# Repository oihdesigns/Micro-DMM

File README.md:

# Update Late August '25: 
I've recently started a new job. It's great, but has longer hours than my previous job. This will negatively affect the amount of time I put into this project...

# Micro-DMM

This is the PCB design and code for a 4.5 digit DMM/ instrumentation module. It is designed and written primairly for Arduino-style development boards.

I've developed this DMM in my work testing and troubleshooting electronics to make my life easier. 

I've had Deep-Wiki index my documentation. It did a mostly okay job. You can read its summary here:

## The main features are:

- The most recent designs have **open-lead detection in voltmeter mode**. I believe this makes it the first voltmeter in exisitance that can automatically, safely, and positively tell the difference between "there is low impedance between these points" vs "current does not and can not flow between these two points." Please see the white paper for details. 
- Using keyboard emulation to directly type values into a computer for me. (Extremely useful when troubleshooting a populated PCB - you can quickly ohm out both the problem board and a good one directly into Excel to look for different impedances between given contacts.)
- Very sensitive low-resistance readings (accurate to better than 0.01 Ohms with proper lead zeroing).
- LED blinks when I'm reading logic level voltage or higher.
- Simultaneous current and voltage measurement abilities (requires a Hall sensor-based ammeter module). 
- Data logging for current and voltage, with customizable triggers to autolog both.

## Raspberry Pi user interface

The repository now includes a Raspberry Pi-friendly interface that mirrors the firmware display and logging features. The UI is written in Python using Tkinter so it ships with Raspberry Pi OS and can run directly on the framebuffer or under X11. To start the dashboard with the built-in demo generator run:

```
python3 -m raspi_port.app
```

In deployment the measurement host should feed real readings to the `MicroDmmApp` class instead of the demo thread. The window presents the same information rendered by `updateDisplay()`—live voltage or resistance with min/max tracking, current when enabled, the active mode, timestamps, delta/null information, and log counters. Interaction hotkeys replace the touch panel:

| Function | Touch color | Hotkey | Description |
| --- | --- | --- | --- |
| Mode cycle | Red | `M` | Advances through the measurement modes. |
| Manual log | Green | `L` | Appends the most recent sample buffer to `~/micro_dmm_logs/data.csv`. |
| Auto log export | – | `A` | Writes the auto-log buffer to `~/micro_dmm_logs/data_autologged.csv`. |
| Min/Max reset | Blue | `Z` | Clears the stored extrema, just like tapping “Min/Max”. |
| Type/Δ | Yellow | `T` | In *Type* mode it writes the displayed value to `typed_entries.txt`; otherwise it arms the delta/null workflow. |

On a Raspberry Pi you can optionally map these controls to hardware buttons by defining a `MICRO_DMM_GPIO` environment variable before launching the program. The value is a comma-separated list such as `mode=5,manual_log=6,auto_log=13,minmax=19,type=26`. Each entry binds a GPIO pin (using `gpiozero.Button`) to the corresponding action.

All log exports stay on the Pi’s filesystem under `~/micro_dmm_logs/`. The CSV layouts match the firmware’s `logCurrentData()` and `autologArraysToCSV()` routines so downstream tooling continues to work. The `typed_entries.txt` file replaces the USB keyboard emulator and captures the same formatted text that would have been “typed” into a host PC, while also echoing it to stdout for quick clipboard-style use.

I have a long and detailed write-up of the circuitry design on my personal website: https://www.oihdesigns.com/arduino-multimeter-project

There are a couple videos here:
https://youtu.be/rzj-ar2Qv_A
and here:
https://youtu.be/hZ4eH-7RNsU

Here are more photos:

## Design Prioities and Compromises:
This meter is designed to complement and support the more expensive equimpent generally found in a lab, rather than replace it. With that in mide, I've made the following design decisions on my priorites:

### Minimal Protections
- The voltmeter circuitry is not designed to measure amplitudes higher than is dangerous to humans. By not designing a tool that is supposed to keep people safe I can dramatically simplify and shrink the design. (The said, I've nailed the voltmeter circuit with a 1000V megaohmmeter. No problem.)
- Likewise, the resistance circuit can be damaged if you accidentally measure too much /unregulated voltage. This is a tradeoff for a very fast and accurate autoranging ohmmeter circuit that can accurately read from less than 0.01 to more than 5,000,000 Ohms. 

### Streamlined Functions
- There is no built in ammeter, inductance, or capacitance function. Ammeter function is easily added as needed with either an off-the-shelf module, or a low value resistor across the voltmeter. There isn't an easy way to add indutance or capacitance. I don't use any of these often enough for them to be worth taking up the PCB space.  

## Current Support:
As of writing I have functional versions (I confirmed the core functions work) that support the:
- Arduino Uno R4
- Arduino Giga (with or without the display shield)
- Arduino ESP32 Nano (via jumpers)
- Seeed Studio XIAO RA4M1 (same processer as the Uno R4)
- I have partial function on a direct computer (Windows 11) interface with a FT232H breakout board (AdaFruit makes a nice one). I can see the data lines and it looks like most of the logic works, more or less. It's a proof of concept port and a test for "can I tell the AI to take an Arduino sketch and port it to Python" (the answer is far more yes than it use to be).
  -  That said, it's very slow (reading in at 2-3sps). I'm not sure how to optimize this, and speeding it up is not an immediate priority. 

# Future Plans:

## Major Function Things to Address:
- Writing to MicroSD cards over the AUX SPI Bux on the RA4M1 XIAO boards. I set this up and tested it, but it didn't work and needs to be troubleshot.
- Getting the code to run on the XIAO RP2350 board. It compiles but does not run. 

## Potential Refinements To-Do List:
- Revise the PCB design to shrink the physical size (the current design was made with hand-soldering in mind). This would involve:
  - Smaller footprint components for things like the pullup resistors.
  - Dedicated multiple transistor packages for the switching functions rather than the discreet components.
  - There are probably other ways to shrink the design.
  - There is some potential performance improvement room to the analog circuit if I take advantage of the ADS1115's max input voltage of ~6.144vdc instead of 5vdc.
- There is always room for cleanup in the code to make it more elegant. 

## Ideas for Expanding on the Current Function / :
- Make a version that uses an ADS1256 instead of the ADS1115 to support measurements speeds up to 30,000 samples/second and resolutions of up to 24bits. (I have had proof-of-concept success with this using a Raspberry PI ADS1256 hat.)
- Make a version that runs off a Raspberry Pi.
- Implement WiFi/Bluetooth features on the boards that support it.
- Implement DAC output as a simple function generator for the boards that support it.
- Add a jumper on the PCB and write the code to allow four-wire resistance readings.

If you're interested in helping develop this please feel free to reach out. 

# FAQ:
- Q: What is the logic voltage?
  - A:  The current PCB works for either 3.3 or 5vdc. 

- Q: Is there voltage isolation on the USB?
  - A: There is enough isolation (500K Ohms) that you will not hurt anything by measuring voltage (in either polarity) on something connected to the wall while the meter is also connected to the wall, but not enough to prevent ground loops from interfering with measurements. See the longer, full write up on my website, and then buy the Adafruit USB voltage isolation board.

- Q: The Adafruit isolation board says "100mA." What does the meter draw?
  - A: With the XIAO RA4M1, 50-60mA typical when measuring voltage. Closer to 100mA when measuring resistance. The resistance circuit goes into low-power mode several seconds after being open (except in a no-sleep mode).

- Q: Does it work on an Arduino Uno R3?
  - A: As a basic meter, yes, but there's no keyboard emulation.    

- Q: Can I buy one?
  - A: Eventually, yes, probably? I do not have a current timeline for bringing these to market. If you want one please reach out to me. If you want to hand-solder it yourself I can sell you a single PCB and maybe some of the components with higher individual costs.

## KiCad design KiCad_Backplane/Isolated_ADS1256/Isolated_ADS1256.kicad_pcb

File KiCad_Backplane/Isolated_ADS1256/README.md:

# Isolated ADS1256 — rev A

This is an isolated 24-bit ADC board, 95 × 62 mm with 4 layers. The ADS1256, its reference, clock and LDOs all sit on the isolated side. SPI crosses a TI ISO7762 (5 kVrms reinforced, 4 forward / 2 reverse channels). Power crosses a Murata MEJ1S0509SC (5 V in, 9 V out, 5.2 kVDC rated, 3 pF isolation capacitance).

Status: generated, routed and checked: ERC 0, DRC 0 at all severities, 0 unconnected, schematic parity 0. It has not been ordered or tested on hardware.

## Channels

| ADS1256 inputs | Function | Scaling | Suggested setup |
|---|---|---|---|
| AIN0 / AIN1 | ±250 VDC differential | Each leg is 3 × 825k + 10k, returned to COM. k = 10k / 2.485 MΩ = 1/248.5, so 250 V gives 1.006 V. **Vin = Vdiff × 248.5** | BUFEN = 1, PGA 4: ±1.25 V full scale = ±310 V |
| AIN2 / AIN3 | 0.1 Ω shunt (RS1, TLMQ2HDR10FTE, 1.5 W) | Kelvin taps through 100 Ω, with 10 nF C0G across the pair. **I = Vdiff / 0.1** | PGA 8: ±625 mV full scale = ±6.25 A. The shunt is rated about 3.8 A continuous. |
| AIN4–7, AINCOM | Broken out on J4 | Each through 1k | — |
| D0–D3 | ADS1256 GPIOs, on J5 (3.3 V logic, isolated) | — | — |

## COM: the isolated reference (read this before connecting anything)

- **COM sits 1.5 V above GNDI.** GNDI is the ADC's own ground. U5 (OPA333) buffers COM, with 47 Ω and 10 µF on its output. This puts every input in the middle of the ADS1256 buffered input range (GNDI to AVDD−2 V, i.e. 0–3 V), so both the shunt and the divider can swing negative relative to COM.
- **COM is the node the measured circuit connects to.** JP1 is bridged by default and ties the shunt's I− end to COM. The shunt therefore defines where the isolated side sits.
- **Do not connect GNDI to the measured circuit as well.** That would short the COM buffer.
- **Common-mode limit:** each HV terminal must stay within about ±370 V of COM. The shunt must stay within about ±1.2 V of COM, which it does when JP1 is bridged.

## Connectors

- **J1 (host):** 5V, GND, VIO, ~SYNC, ~CS, DIN (MOSI), SCLK, ~DRDY, DOUT (MISO), GND.
  - VIO is your logic rail, 2.25–5.5 V.
  - 5 V input current is roughly 80 mA.
  - The isolator outputs default high, so ~CS and ~SYNC idle high when the host is off.
- **J4 (isolated analog):** A4, A5, A6, A7, AINCOM (each through 1k), COM, GNDI, 5VA (AVDD; keep the load at or below 5 mA).
- **J5 (isolated GPIO):** D0, D1, D2, D3, 3V3 (DVDD), GND.
- **J2:** HV+ / HV− screw terminal.
- **J3:** I+ / I− screw terminal.

## Firmware notes

- **~RESET** is held high by a 10k pull-up. Use the RESET command (0xFE) after power-up.
- **D0/CLKOUT** outputs 7.68 MHz after reset. Clear CLK1:0 in ADCON unless you want the clock on J5.
- **Input buffer:** use BUFEN = 1. The divider has about 10 kΩ source impedance, which is too high for the unbuffered input (about 150 kΩ / PGA).

## Isolation

- **Barrier width:** a 5.6 mm copper-free band, set by the MEJ1 module's 5.9 mm pin gap. The ISO7762 has 8 mm internally.
- **HV divider area:** no copper on In1, In2 or B.Cu underneath it. The HV netclass enforces 1.5 mm clearance on F.Cu.
- **Rating:** none of this is a certified insulation rating. Treat the board as basic insulation for a few hundred volts working, and use nylon hardware in the isolated-side mounting holes.

## Files and regenerating

- `tools/design.py` is the single source of truth.
- `tools/make_lib.py` generates `Isolated_ADS1256.kicad_sym` (ADS1256, MEJ1S0509SC, TPS7A4901).
- `tools/gen_sch.py` writes the schematic. `tools/gen_pcb.py` writes the placed, unrouted board. **Running gen_pcb wipes the routing.**
- **Routing flow** (needs a `kicad-cli api-server` running; see `tools/kipc.py`), run in this order:
  1. `stitch_planes.py`
  2. `retry.py --via` for the two LDO thermal pads
  3. `route_pass.py`
  4. `manual_ain.py`: hand-drawn AIN4–7 lanes and Kelvin taps, then +5VA and COM re-routed
  5. `post_silk.py`
  6. a manual U5 GND-to-R6 tie
- Snapshots of each stage are in `build/`.
- Output files: `Isolated_ADS1256_schematic.pdf` and `Isolated_ADS1256_BOM.csv`.

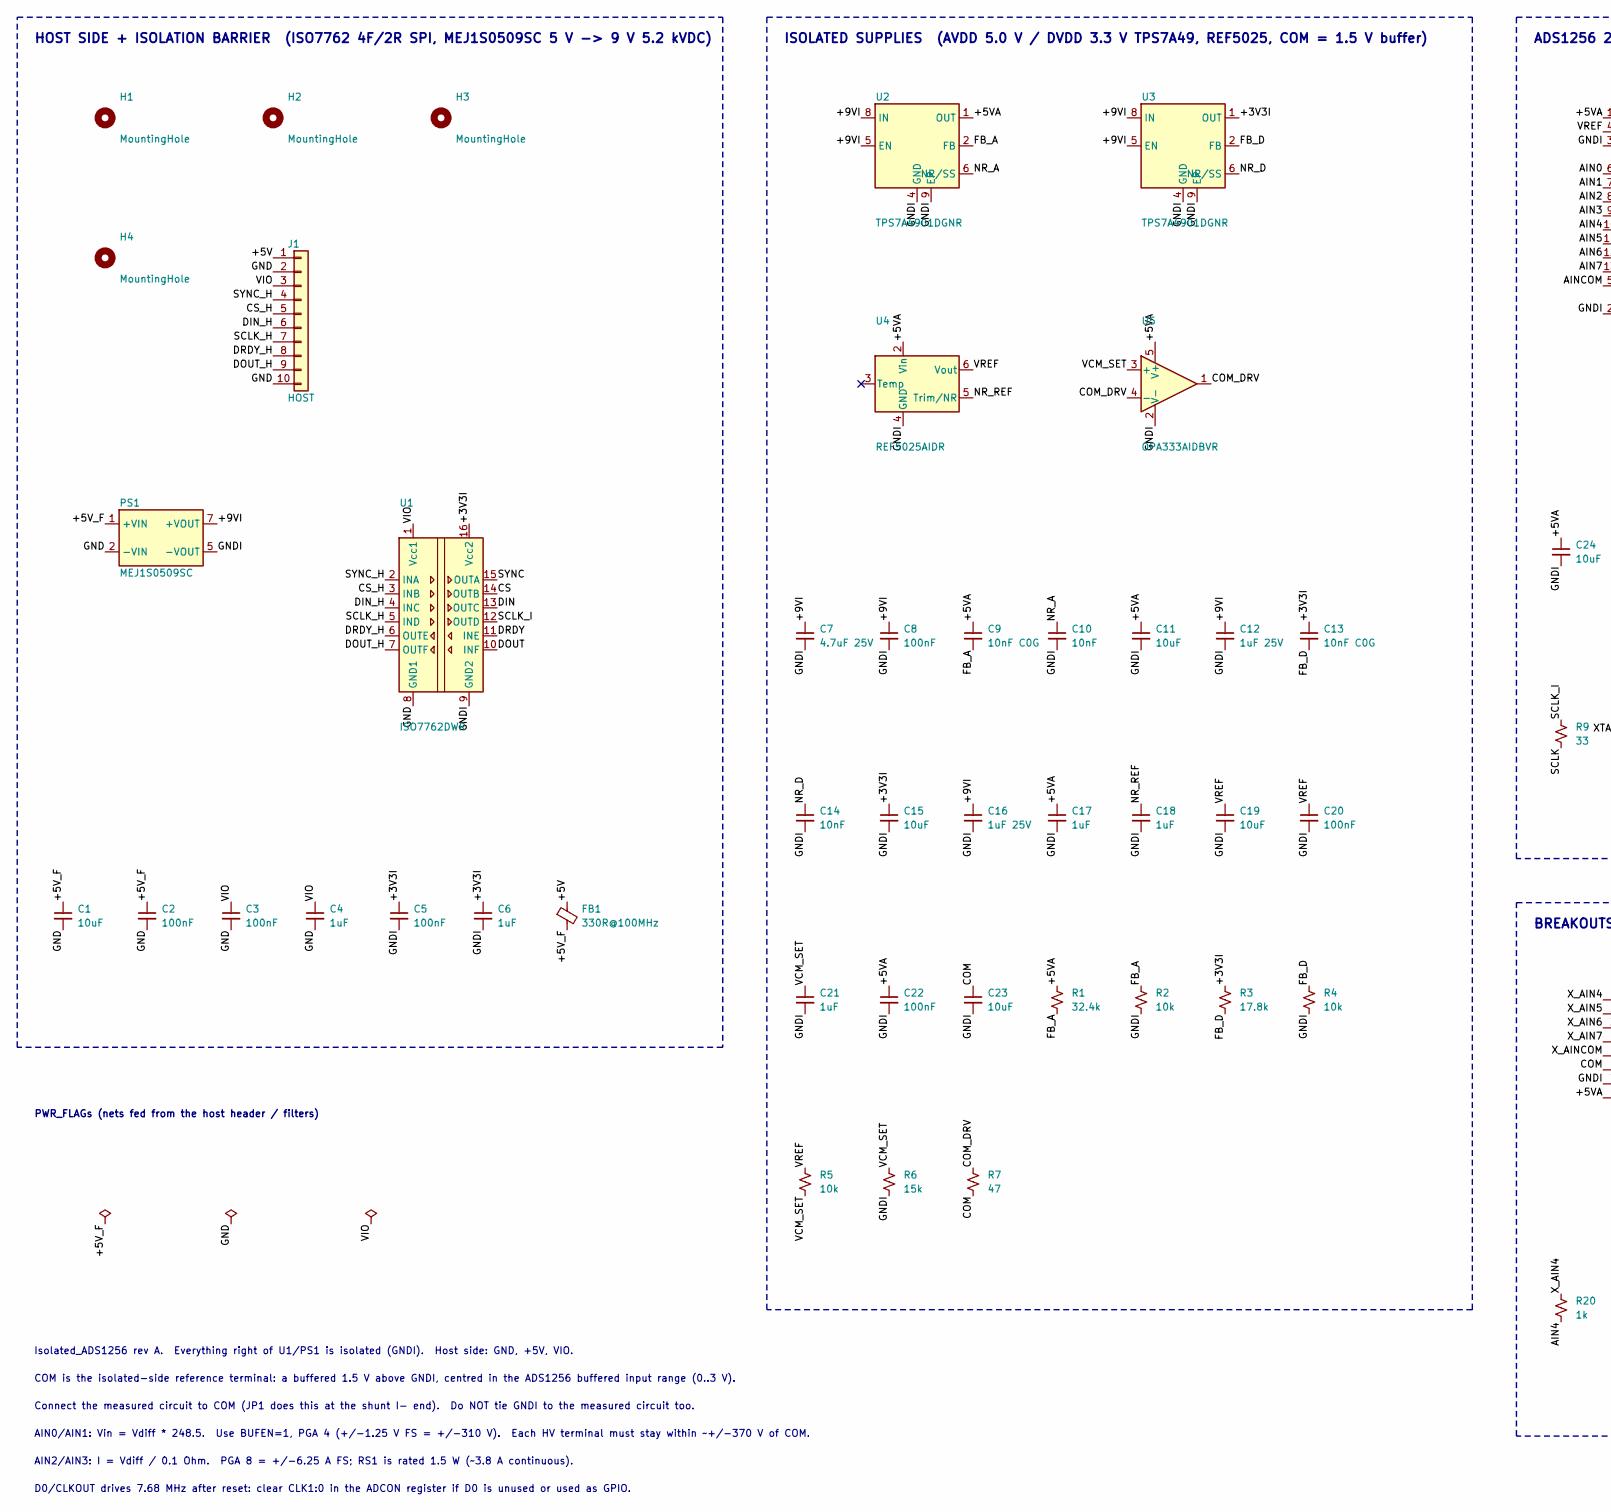
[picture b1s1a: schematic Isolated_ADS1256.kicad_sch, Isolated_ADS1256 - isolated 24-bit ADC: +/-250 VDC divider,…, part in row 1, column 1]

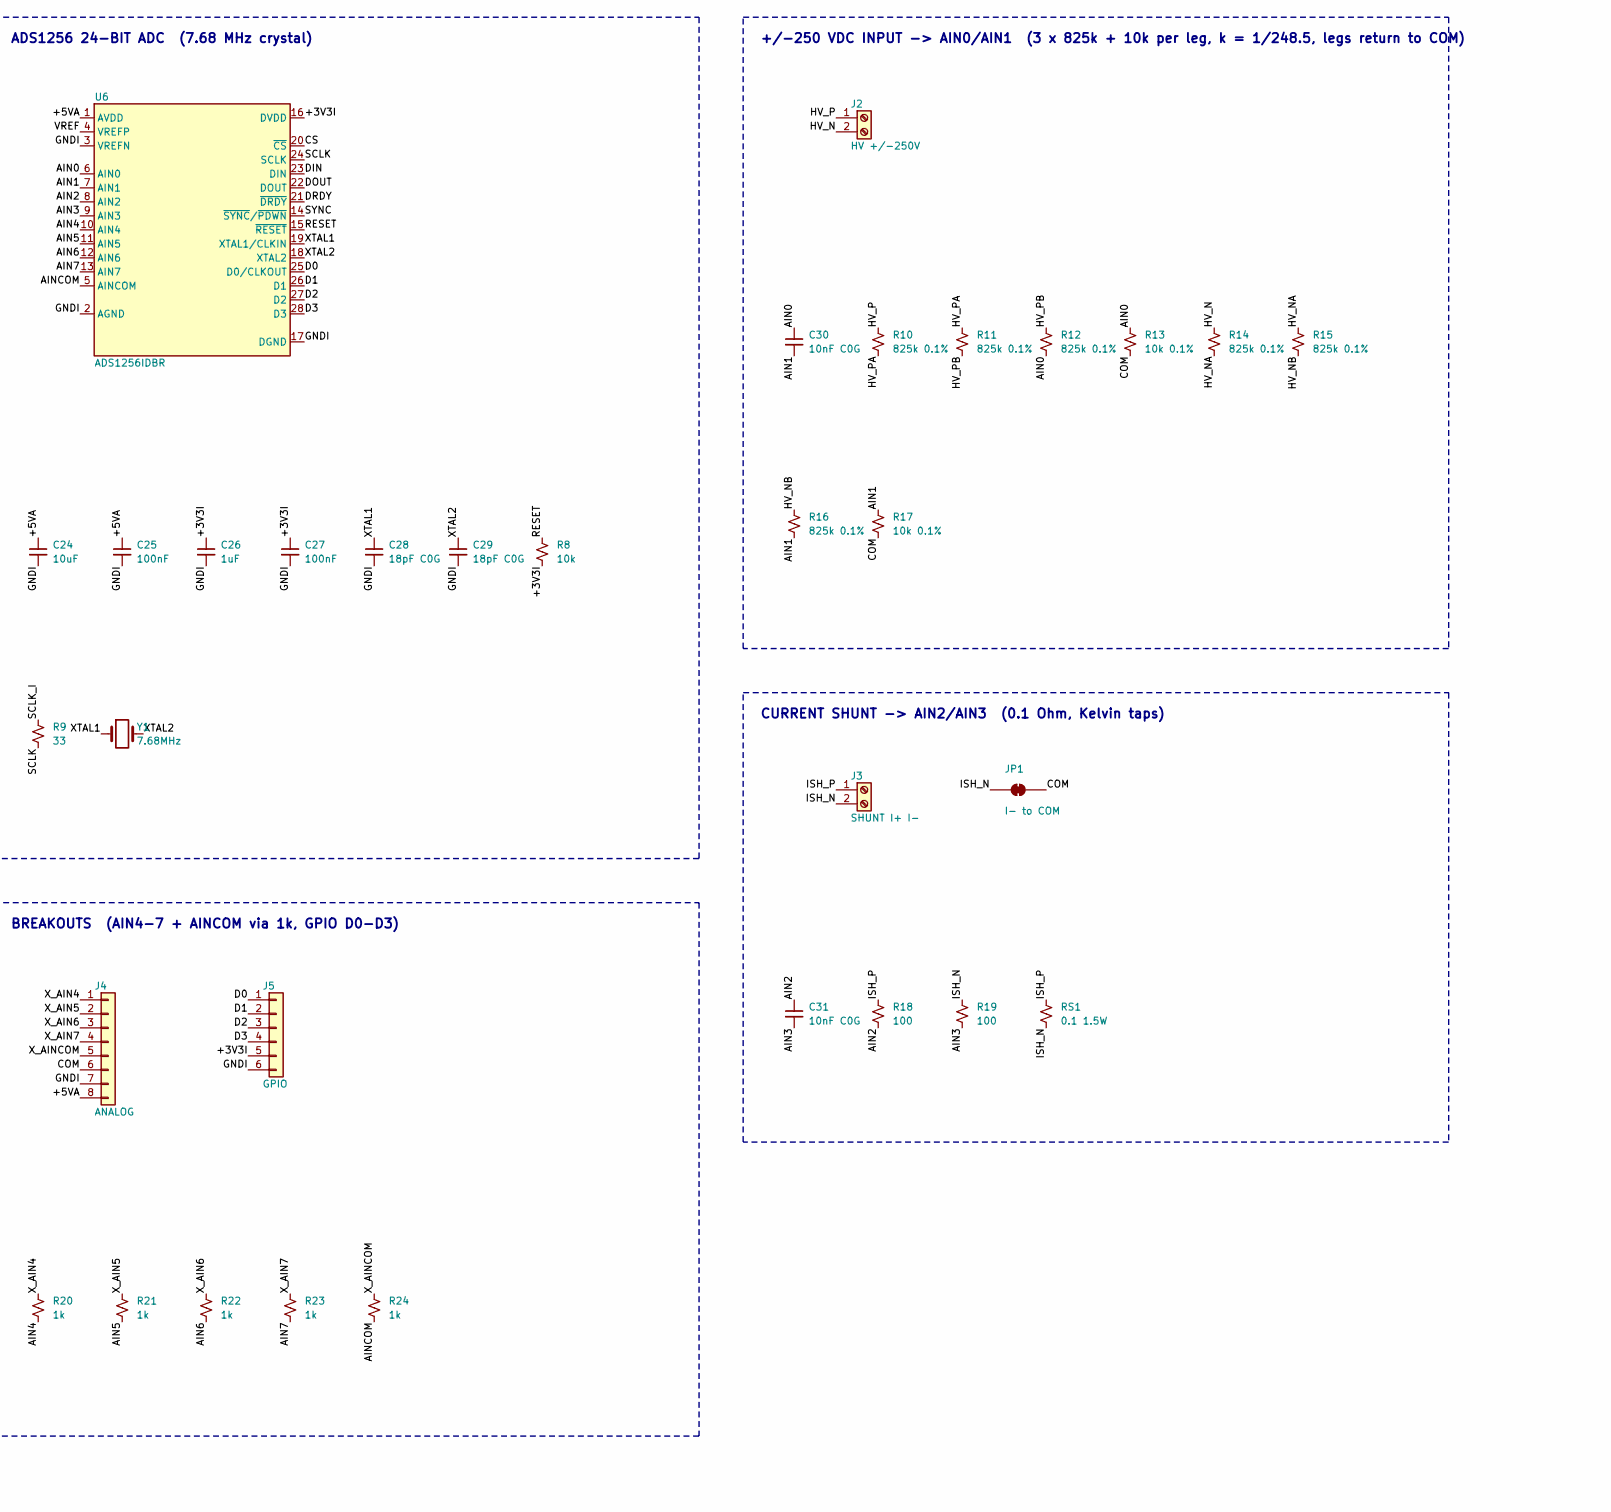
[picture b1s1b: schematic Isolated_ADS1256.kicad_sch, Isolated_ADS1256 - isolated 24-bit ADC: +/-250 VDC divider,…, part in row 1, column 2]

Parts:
C1, C11, C15, C19, C23, C24: 10uF; C_0805_2012Metric_Pad1.18x1.45mm_HandSolder
C2, C3, C5, C8, C20, C22, C25, C27: 100nF; C_0603_1608Metric_Pad1.08x0.95mm_HandSolder
C4, C6, C17, C18, C21, C26: 1uF; C_0603_1608Metric_Pad1.08x0.95mm_HandSolder
C7: 4.7uF 25V; C_0805_2012Metric_Pad1.18x1.45mm_HandSolder
C9, C13: 10nF C0G; C_0603_1608Metric_Pad1.08x0.95mm_HandSolder
C10, C14: 10nF; C_0603_1608Metric_Pad1.08x0.95mm_HandSolder
C12, C16: 1uF 25V; C_0603_1608Metric_Pad1.08x0.95mm_HandSolder
C28, C29: 18pF C0G; C_0603_1608Metric_Pad1.08x0.95mm_HandSolder
C30, C31: 10nF C0G; C_0805_2012Metric_Pad1.18x1.45mm_HandSolder
FB1: 330R@100MHz; L_0805_2012Metric_Pad1.05x1.20mm_HandSolder
H1, H2, H3, H4: MountingHole; MountingHole_3.2mm_M3
J1: HOST; PinHeader_1x10_P2.54mm_Vertical
J2: HV +/-250V; TerminalBlock_RND_205-00232_1x02_P5.08mm_Horizontal
J3: SHUNT I+ I-; TerminalBlock_RND_205-00232_1x02_P5.08mm_Horizontal
J4: ANALOG; PinHeader_1x08_P2.54mm_Vertical
J5: GPIO; PinHeader_1x06_P2.54mm_Vertical
JP1: I- to COM; SolderJumper-2_P1.3mm_Bridged_RoundedPad1.0x1.5mm
PS1: MEJ1S0509SC; Converter_DCDC_muRata_MEJ1SxxxxSC_THT
R1: 32.4k; R_0603_1608Metric_Pad0.98x0.95mm_HandSolder
R2, R4, R5, R8: 10k; R_0603_1608Metric_Pad0.98x0.95mm_HandSolder
R3: 17.8k; R_0603_1608Metric_Pad0.98x0.95mm_HandSolder
R6: 15k; R_0603_1608Metric_Pad0.98x0.95mm_HandSolder
R7: 47; R_0603_1608Metric_Pad0.98x0.95mm_HandSolder
R9: 33; R_0603_1608Metric_Pad0.98x0.95mm_HandSolder
R10, R11, R12, R14, R15, R16: 825k 0.1%; R_1206_3216Metric_Pad1.30x1.75mm_HandSolder
R13, R17: 10k 0.1%; R_0805_2012Metric_Pad1.20x1.40mm_HandSolder
R18, R19: 100; R_0603_1608Metric_Pad0.98x0.95mm_HandSolder
R20, R21, R22, R23, R24: 1k; R_0603_1608Metric_Pad0.98x0.95mm_HandSolder
RS1: 0.1 1.5W; R_2010_5025Metric_Pad1.40x2.65mm_HandSolder
U1: ISO7762DWR; SOIC-16W_7.5x10.3mm_P1.27mm
U2, U3: TPS7A4901DGNR; HVSSOP-8-1EP_3x3mm_P0.65mm_EP1.57x1.89mm
U4: REF5025AIDR; SOIC-8_3.9x4.9mm_P1.27mm
U5: OPA333AIDBVR; SOT-23-5
U6: ADS1256IDBR; SSOP-28_5.3x10.2mm_P0.65mm
Y1: 7.68MHz; Crystal_SMD_HC49-SD

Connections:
/+3V3I: C5.1, C6.1, C13.1, C15.1, C26.1, C27.1, J5.5, R3.1, R8.2, U1.16 (Vcc2), U3.1 (OUT), U6.16 (DVDD)
/+5V: FB1.1, J1.1
/+5VA: C9.1, C11.1, C17.1, C22.1, C24.1, C25.1, J4.8, R1.1, U2.1 (OUT), U4.2 (Vin), U5.5 (V+), U6.1 (AVDD)
/+5V_F: C1.1, C2.1, FB1.2, PS1.1 (+VIN)
/+9VI: C7.1, C8.1, C12.1, C16.1, PS1.7 (+VOUT), U2.5 (EN), U2.8 (IN), U3.5 (EN), U3.8 (IN)
/AIN0: C30.1, R12.2, R13.1, U6.6 (AIN0)
/AIN1: C30.2, R16.2, R17.1, U6.7 (AIN1)
/AIN2: C31.1, R18.2, U6.8 (AIN2)
/AIN3: C31.2, R19.2, U6.9 (AIN3)
/AIN4: R20.2, U6.10 (AIN4)
/AIN5: R21.2, U6.11 (AIN5)
/AIN6: R22.2, U6.12 (AIN6)
/AIN7: R23.2, U6.13 (AIN7)
/AINCOM: R24.2, U6.5 (AINCOM)
/COM: C23.1, J4.6, JP1.2 (B), R7.2, R13.2, R17.2
/COM_DRV: R7.1, U5.1, U5.4 (-)
/CS: U1.14 (OUTB), U6.20 (~CS)
/CS_H: J1.5, U1.3 (INB)
/D0: J5.1, U6.25 (D0/CLKOUT)
/D1: J5.2, U6.26 (D1)
/D2: J5.3, U6.27 (D2)
/D3: J5.4, U6.28 (D3)
/DIN: U1.13 (OUTC), U6.23 (DIN)
/DIN_H: J1.6, U1.4 (INC)
/DOUT: U1.10 (INF), U6.22 (DOUT)
/DOUT_H: J1.9, U1.7 (OUTF)
/DRDY: U1.11 (INE), U6.21 (~DRDY)
/DRDY_H: J1.8, U1.6 (OUTE)
/FB_A: C9.2, R1.2, R2.1, U2.2 (FB)
/FB_D: C13.2, R3.2, R4.1, U3.2 (FB)
/GND: C1.2, C2.2, C3.2, C4.2, J1.2, J1.10, PS1.2 (-VIN), U1.8 (GND1)
/GNDI: C5.2, C6.2, C7.2, C8.2, C10.2, C11.2, C12.2, C14.2, C15.2, C16.2, C17.2, C18.2, C19.2, C20.2, C21.2, C22.2, C23.2, C24.2, C25.2, C26.2, C27.2, C28.2, C29.2, J4.7, J5.6, PS1.5 (-VOUT), R2.2, R4.2, R6.2, U1.9 (GND2), U2.4 (GND), U2.9 (EP), U3.4 (GND), U3.9 (EP), U4.4 (GND), U5.2 (V-), U6.2 (AGND), U6.3 (VREFN), U6.17 (DGND)
/HV_N: J2.2, R14.1
/HV_NA: R14.2, R15.1
/HV_NB: R15.2, R16.1
/HV_P: J2.1, R10.1
/HV_PA: R10.2, R11.1
/HV_PB: R11.2, R12.1
/ISH_N: J3.2, JP1.1 (A), R19.1, RS1.2
/ISH_P: J3.1, R18.1, RS1.1
/NR_A: C10.1, U2.6 (NR/SS)
/NR_D: C14.1, U3.6 (NR/SS)
/NR_REF: C18.1, U4.5 (Trim/NR)
/RESET: R8.1, U6.15 (~RESET)
/SCLK: R9.2, U6.24 (SCLK)
/SCLK_H: J1.7, U1.5 (IND)
/SCLK_I: R9.1, U1.12 (OUTD)
/SYNC: U1.15 (OUTA), U6.14 (~SYNC/~PDWN)
/SYNC_H: J1.4, U1.2 (INA)
/VCM_SET: C21.1, R5.2, R6.1, U5.3 (+)
/VIO: C3.1, C4.1, J1.3, U1.1 (Vcc1)
/VREF: C19.1, C20.1, R5.1, U4.6 (Vout), U6.4 (VREFP)
/XTAL1: C28.1, U6.19 (XTAL1/CLKIN), Y1.1
/XTAL2: C29.1, U6.18 (XTAL2), Y1.2
/X_AIN4: J4.1, R20.1
/X_AIN5: J4.2, R21.1
/X_AIN6: J4.3, R22.1
/X_AIN7: J4.4, R23.1
/X_AINCOM: J4.5, R24.1

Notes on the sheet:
HOST SIDE + ISOLATION BARRIER (ISO7762 4F/2R SPI, MEJ1S0509SC 5 V -> 9 V 5.2 kVDC)
ISOLATED SUPPLIES (AVDD 5.0 V / DVDD 3.3 V TPS7A49, REF5025, COM = 1.5 V buffer)
ADS1256 24-BIT ADC (7.68 MHz crystal)
BREAKOUTS (AIN4-7 + AINCOM via 1k, GPIO D0-D3)
+/-250 VDC INPUT -> AIN0/AIN1 (3 x 825k + 10k per leg, k = 1/248.5, legs return to COM)
CURRENT SHUNT -> AIN2/AIN3 (0.1 Ohm, Kelvin taps)
PWR_FLAGs (nets fed from the host header / filters)
Isolated_ADS1256 rev A. Everything right of U1/PS1 is isolated (GNDI). Host side: GND, +5V, VIO.
COM is the isolated-side reference terminal: a buffered 1.5 V above GNDI, centred in the ADS1256 buffered input range (0..3 V).
Connect the measured circuit to COM (JP1 does this at the shunt I- end). Do NOT tie GNDI to the measured circuit too.
AIN0/AIN1: Vin = Vdiff * 248.5. Use BUFEN=1, PGA 4 (+/-1.25 V FS = +/-310 V). Each HV terminal must stay within ~+/-370 V of COM.
AIN2/AIN3: I = Vdiff / 0.1 Ohm. PGA 8 = +/-6.25 A FS; RS1 is rated 1.5 W (~3.8 A continuous).
D0/CLKOUT drives 7.68 MHz after reset: clear CLK1:0 in the ADCON register if D0 is unused or used as GPIO.

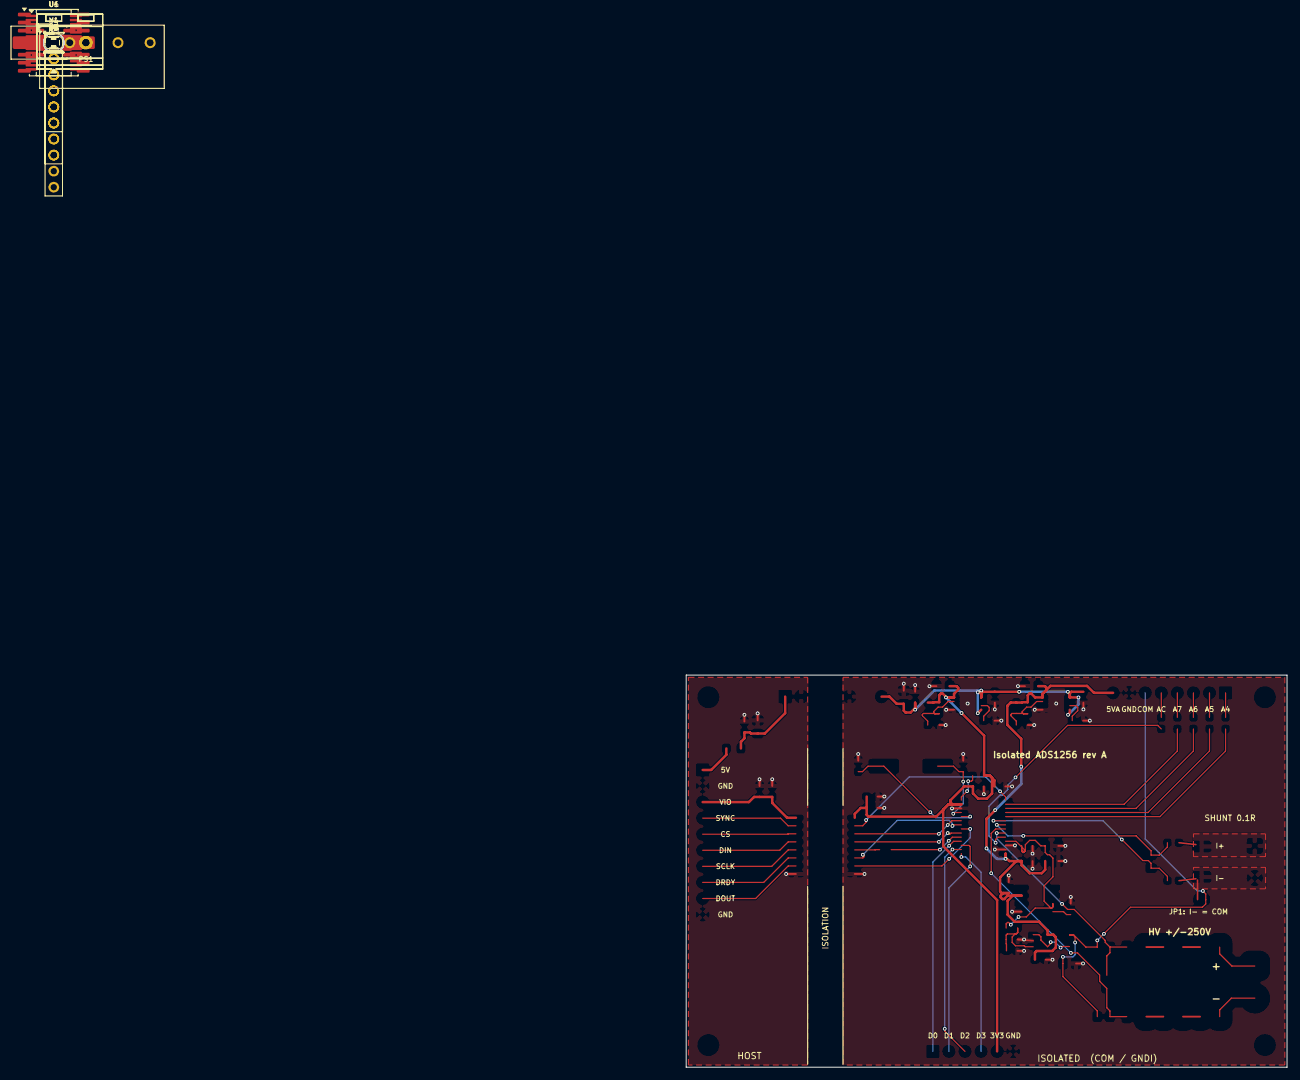
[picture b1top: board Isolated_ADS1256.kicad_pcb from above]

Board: 4 copper layers, 95.0 x 62.0 mm, 75 parts (0 on the bottom side), 59 nets.

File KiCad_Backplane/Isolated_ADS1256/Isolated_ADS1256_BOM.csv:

"Reference","Value","Footprint","PN","QUANTITY","DNP"
"C1,C11,C15,C19,C23,C24","10uF","Capacitor_SMD:C_0805_2012Metric_Pad1.18x1.45mm_HandSolder","GRM21BR61E106KA73L","6",""
"C2,C3,C5,C8,C20,C22,C25,C27","100nF","Capacitor_SMD:C_0603_1608Metric_Pad1.08x0.95mm_HandSolder","GRM188R71H104KA93D","8",""
"C4,C6,C17,C18,C21,C26","1uF","Capacitor_SMD:C_0603_1608Metric_Pad1.08x0.95mm_HandSolder","GRM188R61E105KA12D","6",""
"C7","4.7uF 25V","Capacitor_SMD:C_0805_2012Metric_Pad1.18x1.45mm_HandSolder","GRM21BR61E475KA12L","1",""
"C9,C13","10nF C0G","Capacitor_SMD:C_0603_1608Metric_Pad1.08x0.95mm_HandSolder","GRM1885C1H103JA01D","2",""
"C10,C14","10nF","Capacitor_SMD:C_0603_1608Metric_Pad1.08x0.95mm_HandSolder","GRM188R71H103KA01D","2",""
"C12,C16","1uF 25V","Capacitor_SMD:C_0603_1608Metric_Pad1.08x0.95mm_HandSolder","GRM188R61E105KA12D","2",""
"C28,C29","18pF C0G","Capacitor_SMD:C_0603_1608Metric_Pad1.08x0.95mm_HandSolder","GRM1885C1H180JA01D","2",""
"C30,C31","10nF C0G","Capacitor_SMD:C_0805_2012Metric_Pad1.18x1.45mm_HandSolder","GRM2195C1H103JA01D","2",""
"FB1","330R@100MHz","Inductor_SMD:L_0805_2012Metric_Pad1.05x1.20mm_HandSolder","BLM21PG331SN1D","1",""
"J1","HOST","Connector_PinHeader_2.54mm:PinHeader_1x10_P2.54mm_Vertical","PH1-10-UA","1",""
"J2","HV +/-250V","TerminalBlock_RND:TerminalBlock_RND_205-00232_1x02_P5.08mm_Horizontal","TBJ05-02-1-G-G","1",""
"J3","SHUNT I+ I-","TerminalBlock_RND:TerminalBlock_RND_205-00232_1x02_P5.08mm_Horizontal","TBJ05-02-1-G-G","1",""
"J4","ANALOG","Connector_PinHeader_2.54mm:PinHeader_1x08_P2.54mm_Vertical","PH1-08-UA","1",""
"J5","GPIO","Connector_PinHeader_2.54mm:PinHeader_1x06_P2.54mm_Vertical","PH1-06-UA","1",""
"PS1","MEJ1S0509SC","Converter_DCDC:Converter_DCDC_muRata_MEJ1SxxxxSC_THT","MEJ1S0509SC","1",""
"R1","32.4k","Resistor_SMD:R_0603_1608Metric_Pad0.98x0.95mm_HandSolder","ERJ-3EKF3242V","1",""
"R2,R4,R5,R8","10k","Resistor_SMD:R_0603_1608Metric_Pad0.98x0.95mm_HandSolder","ERJ-3EKF1002V","4",""
"R3","17.8k","Resistor_SMD:R_0603_1608Metric_Pad0.98x0.95mm_HandSolder","ERJ-3EKF1782V","1",""
"R6","15k","Resistor_SMD:R_0603_1608Metric_Pad0.98x0.95mm_HandSolder","ERJ-3EKF1502V","1",""
"R7","47","Resistor_SMD:R_0603_1608Metric_Pad0.98x0.95mm_HandSolder","ERJ-3EKF47R0V","1",""
"R9","33","Resistor_SMD:R_0603_1608Metric_Pad0.98x0.95mm_HandSolder","ERJ-3EKF33R0V","1",""
"R10-R12,R14-R16","825k 0.1%","Resistor_SMD:R_1206_3216Metric_Pad1.30x1.75mm_HandSolder","ERA-8AEB8253V","6",""
"R13,R17","10k 0.1%","Resistor_SMD:R_0805_2012Metric_Pad1.20x1.40mm_HandSolder","ERA-6AEB103V","2",""
"R18,R19","100","Resistor_SMD:R_0603_1608Metric_Pad0.98x0.95mm_HandSolder","ERA-3AEB101V","2",""
"R20-R24","1k","Resistor_SMD:R_0603_1608Metric_Pad0.98x0.95mm_HandSolder","ERJ-3EKF1001V","5",""
"RS1","0.1 1.5W","Resistor_SMD:R_2010_5025Metric_Pad1.40x2.65mm_HandSolder","TLMQ2HDR10FTE","1",""
"U1","ISO7762DWR","Package_SO:SOIC-16W_7.5x10.3mm_P1.27mm","ISO7762DWR","1",""
"U2,U3","TPS7A4901DGNR","Package_SO:HVSSOP-8-1EP_3x3mm_P0.65mm_EP1.57x1.89mm","TPS7A4901DGNR","2",""
"U4","REF5025AIDR","Package_SO:SOIC-8_3.9x4.9mm_P1.27mm","REF5025AIDR","1",""
"U5","OPA333AIDBVR","Package_TO_SOT_SMD:SOT-23-5","OPA333AIDBVR","1",""
"U6","ADS1256IDBR","Package_SO:SSOP-28_5.3x10.2mm_P0.65mm","ADS1256IDBR","1",""
"Y1","7.68MHz","Crystal:Crystal_SMD_HC49-SD","ECS-76.8-18-5PXEN-TR","1",""
